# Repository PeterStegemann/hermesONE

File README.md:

# hermesONE
Custom built remote control system

Add https://github.com/PeterStegemann/Atmel-AVR-CPP to the base directory to build.

This is actually a private project, not meant to be rebuild by others. But maybe some of this code is useful for those who accidentially end up here?

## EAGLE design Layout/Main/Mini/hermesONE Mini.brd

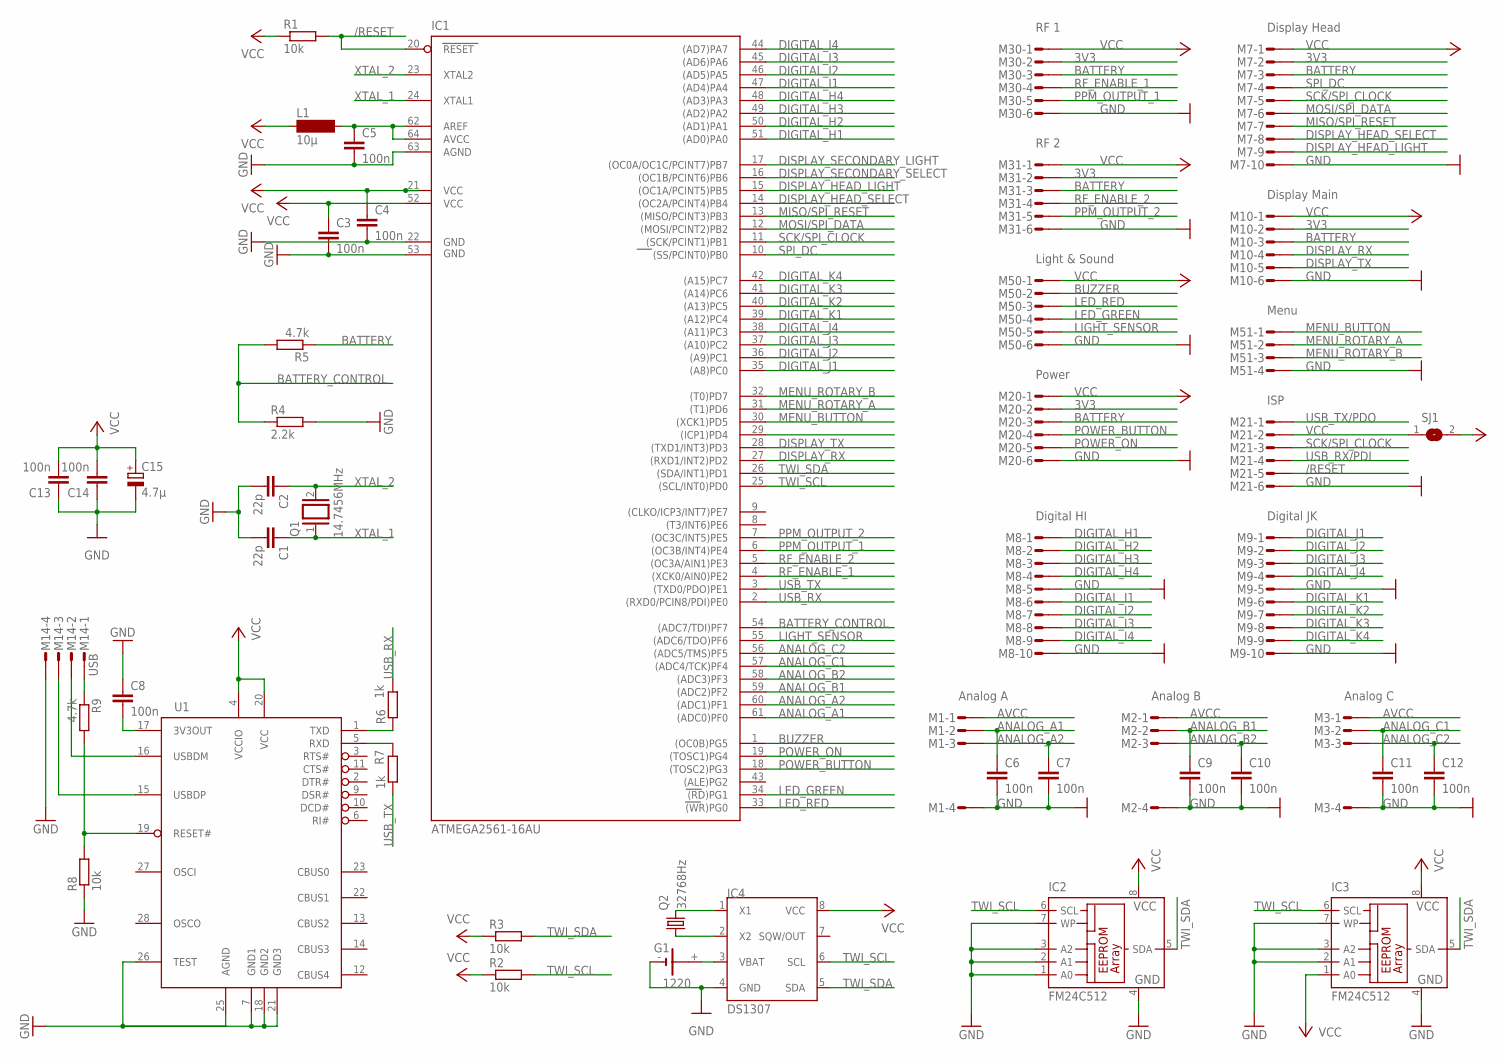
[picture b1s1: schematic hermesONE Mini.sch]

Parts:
C1, C2: 22p; C0603
C3, C4, C5, C6, C7, C8, C9, C10, C11, C12, C13, C14: 100n; C0603
C15: 4.7µ; PANASONIC_B
G1: 1220; KZH12THM
IC1: ATMEGA2561-16AU; TQFP64
IC2, IC3: FM24C512; SO-08M
IC4: DS1307; SOIC-8
L1: 10µ; SM-1206
M1: Analog A; MT-4
M2: Analog B; MT-4
M3: Analog C; MT-4
M7: Display Head; MT-10
M8: Digital HI; MT-10
M9: Digital JK; MT-10
M10: Display Main; MT-6
M14: USB; MT-4
M20: Power; MT-6
M21: ISP; MT-6
M30: RF 1; MT-6
M31: RF 2; MT-6
M50: Light & Sound; MT-6
M51: Menu; MT-4
Q1: 14.7456MHz; QS
Q2: 32768Hz; TC26H
R1, R2, R3, R8: 10k; R0603
R4: 2.2k; R0603
R5, R9: 4.7k; R0603
R6, R7: 1k; R0603
SJ1: SJ
U1: FT232RL; SSOP28DB

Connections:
3V3: M7.2, M10.2, M20.2, M30.2, M31.2
/RESET: IC1.20 (RESET), M21.5, R1.2
ANALOG_A1: C6.1, IC1.61 ((ADC0)PF0), M1.2
ANALOG_A2: C7.1, IC1.60 ((ADC1)PF1), M1.3
ANALOG_B1: C9.1, IC1.59 ((ADC2)PF2), M2.2
ANALOG_B2: C10.1, IC1.58 ((ADC3)PF3), M2.3
ANALOG_C1: C11.1, IC1.57 ((ADC4/TCK)PF4), M3.2
ANALOG_C2: C12.1, IC1.56 ((ADC5/TMS)PF5), M3.3
AVCC: M1.1, M2.1, M3.1
BATTERY: M7.3, M10.3, M20.3, M30.3, M31.3, R5.1
BATTERY_CONTROL: IC1.54 ((ADC7/TDI)PF7), R4.1, R5.2
BUZZER: IC1.1 ((OC0B)PG5), M50.2
DIGITAL_H1: IC1.51 ((AD0)PA0), M8.1
DIGITAL_H2: IC1.50 ((AD1)PA1), M8.2
DIGITAL_H3: IC1.49 ((AD2)PA2), M8.3
DIGITAL_H4: IC1.48 ((AD3)PA3), M8.4
DIGITAL_I1: IC1.47 ((AD4)PA4), M8.6
DIGITAL_I2: IC1.46 ((AD5)PA5), M8.7
DIGITAL_I3: IC1.45 ((AD6)PA6), M8.8
DIGITAL_I4: IC1.44 ((AD7)PA7), M8.9
DIGITAL_J1: IC1.35 ((A8)PC0), M9.1
DIGITAL_J2: IC1.36 ((A9)PC1), M9.2
DIGITAL_J3: IC1.37 ((A10)PC2), M9.3
DIGITAL_J4: IC1.38 ((A11)PC3), M9.4
DIGITAL_K1: IC1.39 ((A12)PC4), M9.6
DIGITAL_K2: IC1.40 ((A13)PC5), M9.7
DIGITAL_K3: IC1.41 ((A14)PC6), M9.8
DIGITAL_K4: IC1.42 ((A15)PC7), M9.9
DISPLAY_HEAD_LIGHT: IC1.15 ((OC1A/PCINT5)PB5), M7.9
DISPLAY_HEAD_SELECT: IC1.14 ((OC2A/PCINT4)PB4), M7.8
DISPLAY_RX: IC1.27 ((RXD1/INT2)PD2), M10.4
DISPLAY_SECONDARY_LIGHT: IC1.17 ((OC0A/OC1C/PCINT7)PB7)
DISPLAY_SECONDARY_SELECT: IC1.16 ((OC1B/PCINT6)PB6)
DISPLAY_TX: IC1.28 ((TXD1/INT3)PD3), M10.5
GND: C1.2, C2.2, C3.2, C4.2, C5.2, C6.2, C7.2, C8.1, C9.2, C10.2, C11.2, C12.2, C13.1, C14.1, C15.-, G1.-, IC1.22 (GND), IC1.53 (GND1), IC1.63 (AGND), IC2.1 (A0), IC2.2 (A1), IC2.3 (A2), IC2.4 (GND), IC2.7 (WP), IC3.2 (A1), IC3.3 (A2), IC3.4 (GND), IC3.7 (WP), IC4.4 (GND), M1.4, M2.4, M3.4, M7.10, M8.5, M8.10, M9.5, M9.10, M10.6, M14.4, M20.6, M21.6, M30.6, M31.6, M50.6, M51.4, R4.2, R8.1, U1.7 (GND1), U1.18 (GND2), U1.21 (GND3), U1.25 (AGND), U1.26 (TEST)
LED_GREEN: IC1.34 ((RD)PG1), M50.4
LED_RED: IC1.33 ((WR)PG0), M50.3
LIGHT_SENSOR: IC1.55 ((ADC6/TDO)PF6), M50.5
MENU_BUTTON: IC1.30 ((XCK1)PD5), M51.1
MENU_ROTARY_A: IC1.31 ((T1)PD6), M51.2
MENU_ROTARY_B: IC1.32 ((T0)PD7), M51.3
MISO/SPI_RESET: IC1.13 ((MISO/PCINT3)PB3), M7.7
MOSI/SPI_DATA: IC1.12 ((MOSI/PCINT2)PB2), M7.6
unnamed: M14.3, U1.15 (USBDP)
unnamed: G1.+, IC4.3 (VBAT)
unnamed: IC4.2 (X2), Q2.1
unnamed: M14.2, U1.16 (USBDM)
unnamed: C5.1, IC1.62 (AREF), IC1.64 (AVCC), L1.2
unnamed: IC4.1 (X1), Q2.2
unnamed: M21.2, SJ1.1
unnamed: R6.1, U1.1 (TXD)
unnamed: R7.1, U1.5 (RXD)
unnamed: M14.1, R9.1
unnamed: R8.2, R9.2, U1.19 (RESET#)
unnamed: C8.2, U1.17 (3V3OUT)
POWER_BUTTON: IC1.18 ((TOSC2)PG3), M20.4
POWER_ON: IC1.19 ((TOSC1)PG4), M20.5
PPM_INPUT: IC1.29 ((ICP1)PD4)
PPM_OUTPUT_1: IC1.6 ((OC3B/INT4)PE4), M30.5
PPM_OUTPUT_2: IC1.7 ((OC3C/INT5)PE5), M31.5
RF_ENABLE_1: IC1.4 ((XCK0/AIN0)PE2), M30.4
RF_ENABLE_2: IC1.5 ((OC3A/AIN1)PE3), M31.4
SCK/SPI_CLOCK: IC1.11 ((SCK/PCINT1)PB1), M7.5, M21.3
SPI_DC: IC1.10 ((SS/PCINT0)PB0), M7.4
TWI_SCL: IC1.25 ((SCL/INT0)PD0), IC2.6 (SCL), IC3.6 (SCL), IC4.6 (SCL), R2.2
TWI_SDA: IC1.26 ((SDA/INT1)PD1), IC2.5 (SDA), IC3.5 (SDA), IC4.5 (SDA), R3.2
USB_RX: IC1.2 ((RXD0/PCIN8/PDI)PE0), R6.2
USB_RX/PDI: M21.4
USB_TX: IC1.3 ((TXD0/PDO)PE1), R7.2
USB_TX/PDO: M21.1
VCC: C3.1, C4.1, C13.2, C14.2, C15.+, IC1.21 (VCC), IC1.52 (VCC1), IC2.8 (VCC), IC3.1 (A0), IC3.8 (VCC), IC4.8 (VCC), L1.1, M7.1, M10.1, M20.1, M30.1, M31.1, M50.1, R1.1, R2.1, R3.1, SJ1.2, U1.4 (VCCIO), U1.20 (VCC)
XTAL_1: C1.1, IC1.24 (XTAL1), Q1.1
XTAL_2: C2.1, IC1.23 (XTAL2), Q1.2

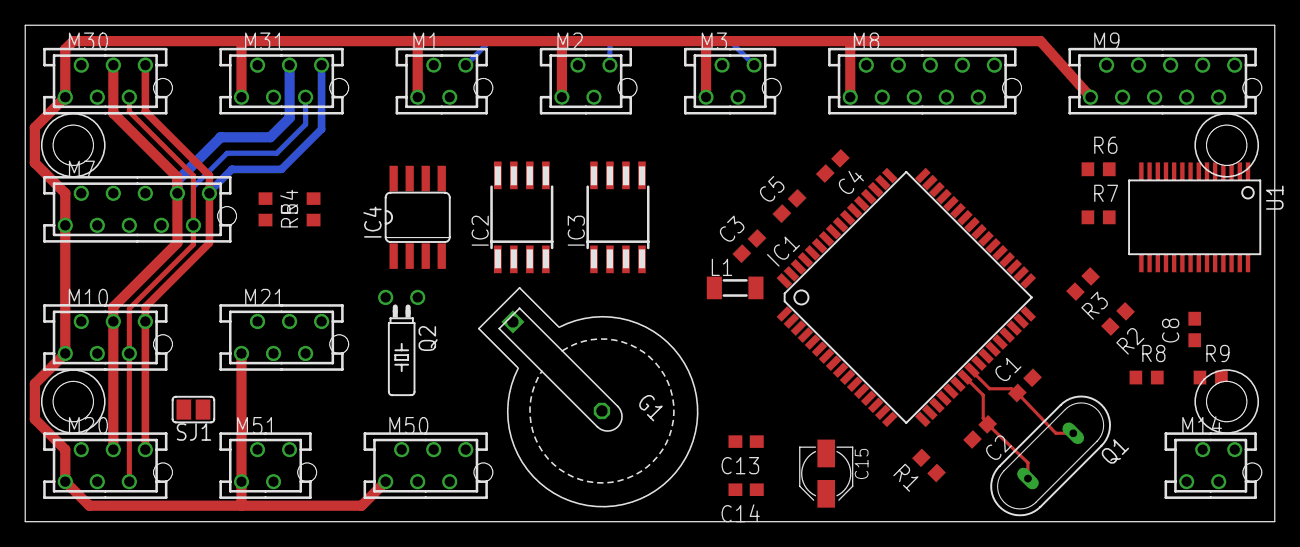
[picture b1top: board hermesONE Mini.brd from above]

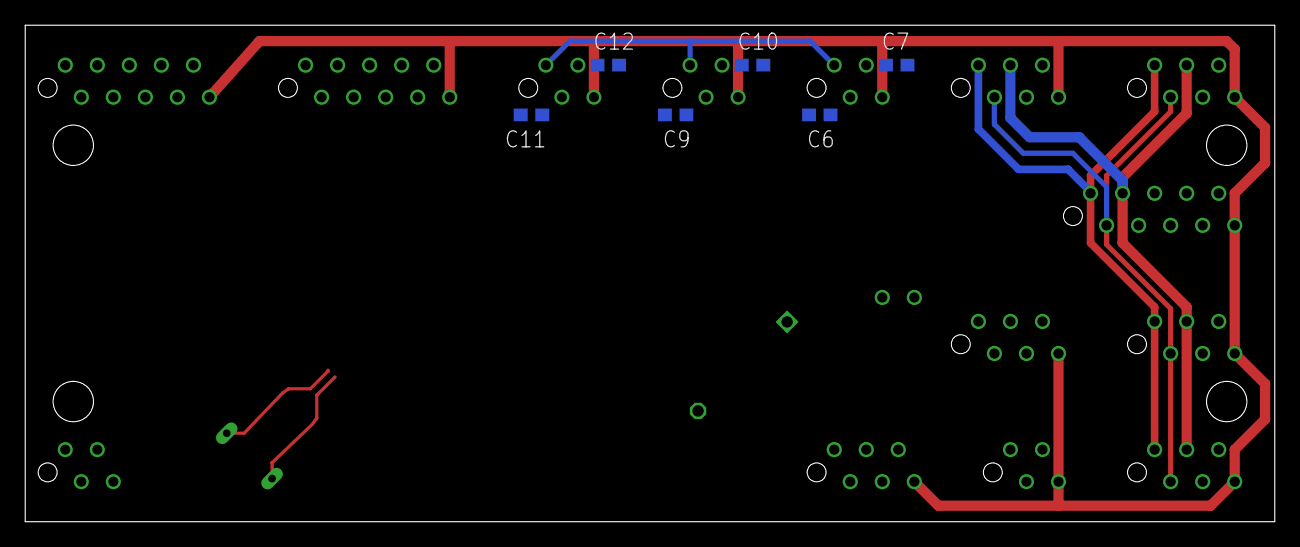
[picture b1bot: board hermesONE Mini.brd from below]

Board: 2 copper layers, 99.1 x 39.4 mm, 48 parts (6 on the bottom side), 68 nets.

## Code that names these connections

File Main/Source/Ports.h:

// Copyright 2007 Peter Stegemann

#ifndef PORTS_H
#define PORTS_H

#include "System.h"

#include <avr/io.h>

// EEPROM
#define EEPROM_PORT									PORTD
#define EEPROM_DDR									DDRD

#define EEPROM_SCL									PD0
#define EEPROM_SDA									PD1

// SPI
#define SPI_PORT									PORTB
#define SPI_DDR										DDRB

#define SPI_SS										PB0
#define SPI_CLOCK									PB1					// Clock
#define SPI_DATA_OUTPUT								PB2					// Send Data
#define SPI_RESET									PB3					// Reset SPI devices
#define SPI_DC										PB0					// Data/Command

#define SPI_0_SELECT								LCD_DOG_SELECT		// Cable Select

// LCD DOG
#define LCD_DOG_SPI_ID								0					// SPI Select

#define LCD_DOG_TIMERA								TCCR1A
#define LCD_DOG_TIMERB								TCCR1B

#define LCD_DOG_PORT								PORTB
#define LCD_DOG_DDR									DDRB

#define LCD_DOG_SELECT								PB4					// Cable Select
#define LCD_DOG_LIGHT								PB5					// Light on/off

// Beep
#define BUZZER_PORT									PORTD
#define BUZZER_DDR									DDRD

#define BUZZER_NOISE								PD4

// Input misc
#define INPUT_TIMERA								TCCR0A
#define INPUT_TIMERB								TCCR0B

#define INPUT_MENU_PORT								PORTD
#define INPUT_MENU_DDR								DDRD
#define INPUT_MENU_PIN								PIND

#define INPUT_MENU_ROTARY_BUTTON					PD5
#define INPUT_MENU_ROTARY_A							PD6
#define INPUT_MENU_ROTARY_B							PD7

#if( SYSTEM_VERSION == SYSTEM_VERSION_MINI_V1)
	#define INPUT_ANALOG_PORTS						8
#elif( SYSTEM_VERSION == SYSTEM_VERSION_V1)
	#define INPUT_ANALOG_PORTS						16
#endif

#define INPUT_ANALOG_PORT_LIGHT						6
#define INPUT_ANALOG_PORT_VOLTAGE					7

#define INPUT_ANALOG_A_D_PORT						PORTF
#define INPUT_ANALOG_A_D_DDR						DDRF
#define INPUT_ANALOG_A_D_PIN						PINF

#if( SYSTEM_VERSION == SYSTEM_VERSION_V1)
	#define INPUT_ANALOG_E_G_PORT					PORTK
	#define INPUT_ANALOG_E_G_DDR					DDRK
	#define INPUT_ANALOG_E_G_PIN					PINK
#endif

#if( SYSTEM_VERSION == SYSTEM_VERSION_MINI_V1)
	#define INPUT_DIGITAL_PORTS						16
#elif( SYSTEM_VERSION == SYSTEM_VERSION_V1)
	#define INPUT_DIGITAL_PORTS						32
#endif

#define INPUT_DIGITAL_H_I_PORT						PORTA
#define INPUT_DIGITAL_H_I_DDR						DDRA
#define INPUT_DIGITAL_H_I_PIN						PINA

#define INPUT_DIGITAL_J_K_PORT						PORTC
#define INPUT_DIGITAL_J_K_DDR						DDRC
#define INPUT_DIGITAL_J_K_PIN						PINC

#if( SYSTEM_VERSION == SYSTEM_VERSION_V1)
	#define INPUT_DIGITAL_L_M_PORT					PORTJ
	#define INPUT_DIGITAL_L_M_DDR					DDRJ
	#define INPUT_DIGITAL_L_M_PIN					PINJ

	#define INPUT_DIGITAL_N_O_PORT					PORTL
	#define INPUT_DIGITAL_N_O_DDR					DDRL
	#define INPUT_DIGITAL_N_O_PIN					PINL
#endif

// Serial communication
#define SERIAL_SYSTEM_PORT							PORTE
#define SERIAL_SYSTEM_DDR							DDRE
#define SERIAL_SYSTEM_PIN							PINE

#define SERIAL_SYSTEM_RX							PE1
#define SERIAL_SYSTEM_TX							PE0

#define SERIAL_DISPLAY_PORT							PORTD
#define SERIAL_DISPLAY_DDR							DDRD
#define SERIAL_DISPLAY_PIN							PIND

#define SERIAL_DISPLAY_RX							PD0
#define SERIAL_DISPLAY_TX							PD1

// PPM generation
#if( SYSTEM_VERSION == SYSTEM_VERSION_V1)
	#define SIGNAL_SERVICE_TIMERA					TCCR4A
	#define SIGNAL_SERVICE_PORT						PORTH
	#define SIGNAL_SERVICE_DDR						DDRH
	#define SIGNAL_SERVICE_PIN						PINH

	#define SIGNAL_SERVICE_PPM_ENABLE_1				PH2
	#define SIGNAL_SERVICE_PPM_ENABLE_2				PH3
	#define SIGNAL_SERVICE_PPM_OUTPUT_1				PH4
	#define SIGNAL_SERVICE_PPM_OUTPUT_2				PH5
#elif( SYSTEM_VERSION == SYSTEM_VERSION_MINI_V1)
	#define SIGNAL_SERVICE_TIMERA					TCCR3A
	#define SIGNAL_SERVICE_PORT						PORTE
	#define SIGNAL_SERVICE_DDR						DDRE
	#define SIGNAL_SERVICE_PIN						PINE

	#define SIGNAL_SERVICE_PPM_ENABLE_1				PE2
	#define SIGNAL_SERVICE_PPM_ENABLE_2				PE7
	#define SIGNAL_SERVICE_PPM_OUTPUT_1				PE3
	#define SIGNAL_SERVICE_PPM_OUTPUT_2				PE4
/*
	#define SIGNAL_SERVICE_PPM_ENABLE_1				PE2
	#define SIGNAL_SERVICE_PPM_ENABLE_2				PE3
	#define SIGNAL_SERVICE_PPM_OUTPUT_1				PE4
	#define SIGNAL_SERVICE_PPM_OUTPUT_2				PE5
*/
#endif

// Status
#define STATUS_SERVICE_PORT							PORTG
#define STATUS_SERVICE_DDR							DDRG

#define STATUS_SERVICE_RED							PG0
#define STATUS_SERVICE_GREEN						PG1

#endif

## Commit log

2020-04-27 Add git ignore file
2020-04-27 Initial add
2020-04-27 Make includes work again
2020-05-01 Fix dependencies
2020-05-01 Update git ignore
2020-05-01 Fix git ignore, update xcode projects
2020-05-01 Add case design
2020-05-01 Add Oled board
2020-05-01 Add power board
2020-05-01 Add status display layout
2020-05-01 Add main boards
2022-11-12 Add desktop client
2022-11-13 Refactor code style, add tests
2022-11-13 Add Lombok
2022-11-14 Introduce dependency injection
2022-11-16 More refactoring
2022-11-30 Refactor configuration file writing
2022-12-10 Cleanups and fixes
2022-12-13 Code style refactoring
2023-04-22 Fix serial configuration transfer
2023-04-22 Fixes and cleanups
2023-04-22 Clean up project structure
2023-04-23 Refactoring of project structure
2023-04-23 Add MacOS app
2023-04-24 Cleanups, fix startup problem
2023-04-24 Cleanups
2023-05-03 Remove xcode support
2023-05-03 Use pragma once for multiple include avoidance
2023-05-04 Rework ui components
2023-05-05 Re-add missing file.
2023-08-08 Inline status components
2023-08-13 Fix for gcc 12
2024-04-18 Clean up layout files
2024-04-18 Fixes for new board
2024-05-06 Fixes for new board, clean up Oled project
2024-05-25 All sorts of fixes and changes to remove stack overruns
2024-05-25 Release 1.1
2024-05-26 Fix building of version without setup display
2024-05-26 Fix for startup without setup display
2024-05-26 Try new marker with better visibility
2024-05-27 Refactor font
2024-05-28 Introduce namespaces
2024-05-28 Add more namespaces
2024-05-28 Rearrange source files
2024-05-30 Fix battery calibration
2024-05-30 Clean up
2024-06-05 Fix blinking on text input
2024-06-06 More inlining
2024-06-08 Restructuring
2024-06-12 Fix configuration handling
2024-06-14 Add missing files for app
2024-06-21 Add manual re-ordering of sources
2024-06-22 Add manual re-ordering of modules and types
2024-06-29 Add validation
2024-07-03 Add total storage size
2024-07-03 Add storage size output
2024-07-03 Add serial transfer of storage size and cleaning of excess configuration entries
2024-09-28 Split twi code from eeprom code
2024-09-28 Remove service access from constructors
2024-09-28 Remove more global dependencies
2024-09-28 Simplify eeprom code
